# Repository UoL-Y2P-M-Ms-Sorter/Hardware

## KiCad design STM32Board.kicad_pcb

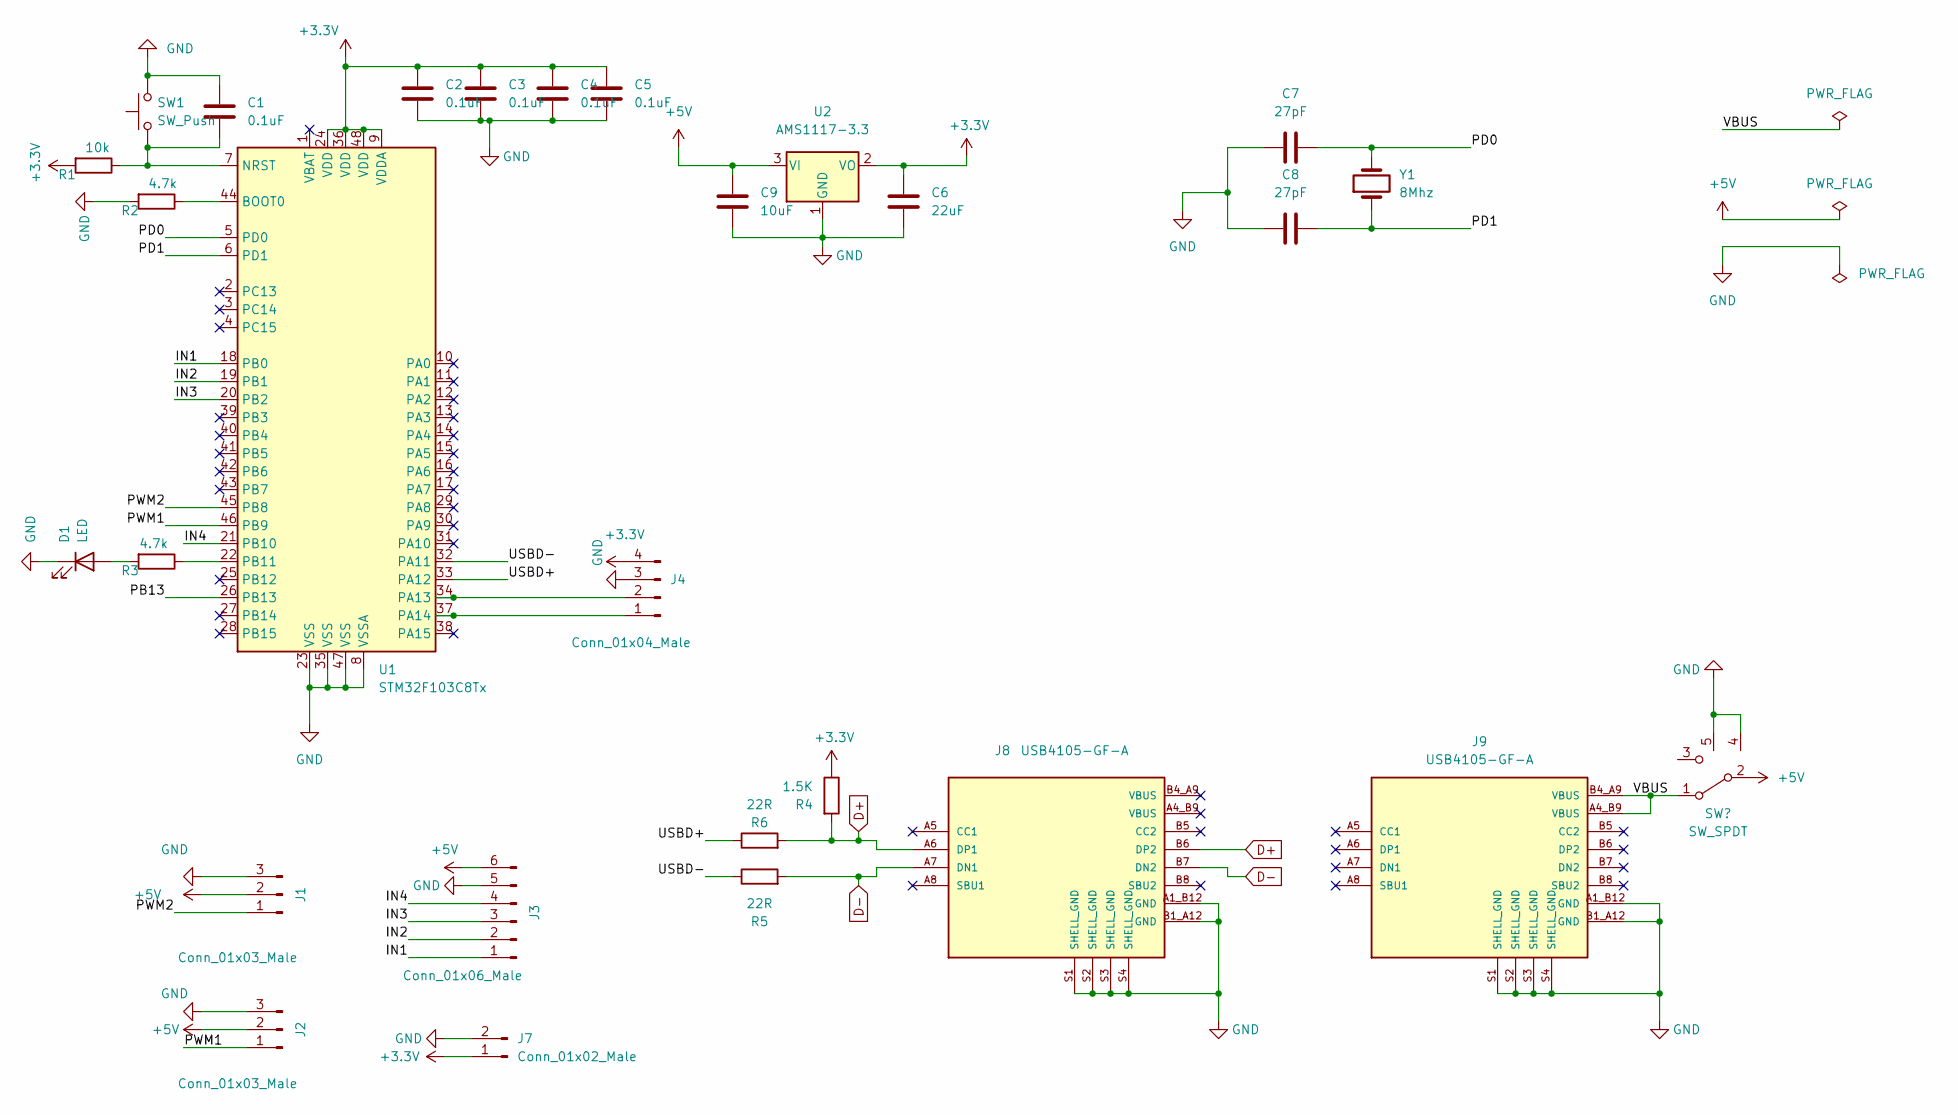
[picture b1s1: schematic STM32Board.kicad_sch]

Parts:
C1, C2, C3, C4, C5: 0.1uF; C_0603_1608Metric
C6: 22uF; CP_EIA-3216-18_Kemet-A
C7, C8: 27pF; C_0603_1608Metric
C9: 10uF; C_0603_1608Metric
D1: LED; LED_0805_2012Metric_Pad1.15x1.40mm_HandSolder
J1, J2: Conn_01x03_Male; PinHeader_1x03_P2.54mm_Vertical
J3: Conn_01x06_Male; PinHeader_1x06_P2.54mm_Vertical
J4: Conn_01x04_Male; PinHeader_1x04_P2.54mm_Vertical
J7: Conn_01x02_Male; PinHeader_1x02_P2.54mm_Vertical
J8, J9: USB4105-GF-A; GCT_USB4105-GF-A; PARTREV A3
R1: 10k; R_0603_1608Metric
R2, R3: 4.7k; R_0603_1608Metric
R4: 1.5K; R_0603_1608Metric
R5, R6: 22R; R_0603_1608Metric
SW1: SW_Push; SW_Push_SPST_NO_Alps_SKRK
U1: STM32F103C8Tx; LQFP-48_7x7mm_P0.5mm
U2: AMS1117-3.3; SOT-223-3_TabPin2
Y1: 8Mhz; Crystal_HC49-4H_Vertical

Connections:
+3V3: C2.2, C3.2, C4.2, C5.2, C6.1, J4.4, J7.1, R1.2, R4.1, U1.9 (VDDA), U1.24 (VDD), U1.36 (VDD), U1.48 (VDD), U2.2 (VO)
+5V: C9.1, J1.2, J2.2, J3.6, U2.3 (VI); also elsewhere on the board
/IN1: J3.1, U1.18 (PB0)
/IN2: J3.2, U1.19 (PB1)
/IN3: J3.3, U1.20 (PB2)
/IN4: J3.4, U1.21 (PB10)
/PB13: U1.26 (PB13)
/PD0: C7.2, U1.5 (PD0), Y1.2
/PD1: C8.2, U1.6 (PD1), Y1.1
/PWM1: J2.1, U1.46 (PB9)
/PWM2: J1.1, U1.45 (PB8)
/USBD+: R6.1, U1.33 (PA12)
/USBD-: R5.1, U1.32 (PA11)
/VBUS: J9.A4_B9 (VBUS), J9.B4_A9 (VBUS); also elsewhere on the board
D+: J8.A6 (DP1), J8.B6 (DP2), R4.2, R6.2
D-: J8.A7 (DN1), J8.B7 (DN2), R5.2
GND: C1.2, C2.1, C3.1, C4.1, C5.1, C6.2, C7.1, C8.1, C9.2, D1.1 (K), J1.3, J2.3, J3.5, J4.3, J7.2, J8.A1_B12 (GND), J8.B1_A12 (GND), J8.S1 (SHELL_GND), J8.S2 (SHELL_GND), J8.S3 (SHELL_GND), J8.S4 (SHELL_GND), J9.A1_B12 (GND), J9.B1_A12 (GND), J9.S1 (SHELL_GND), J9.S2 (SHELL_GND), J9.S3 (SHELL_GND), J9.S4 (SHELL_GND), R2.2, SW1.2, U1.8 (VSSA), U1.23 (VSS), U1.35 (VSS), U1.47 (VSS), U2.1 (GND); also elsewhere on the board
unnamed: C1.1, R1.1, SW1.1, U1.7 (NRST)
unnamed: D1.2 (A), R3.2
unnamed: J4.1, U1.37 (PA14)
unnamed: J4.2, U1.34 (PA13)
unnamed: R2.1, U1.44 (BOOT0)
unnamed: R3.1, U1.22 (PB11)

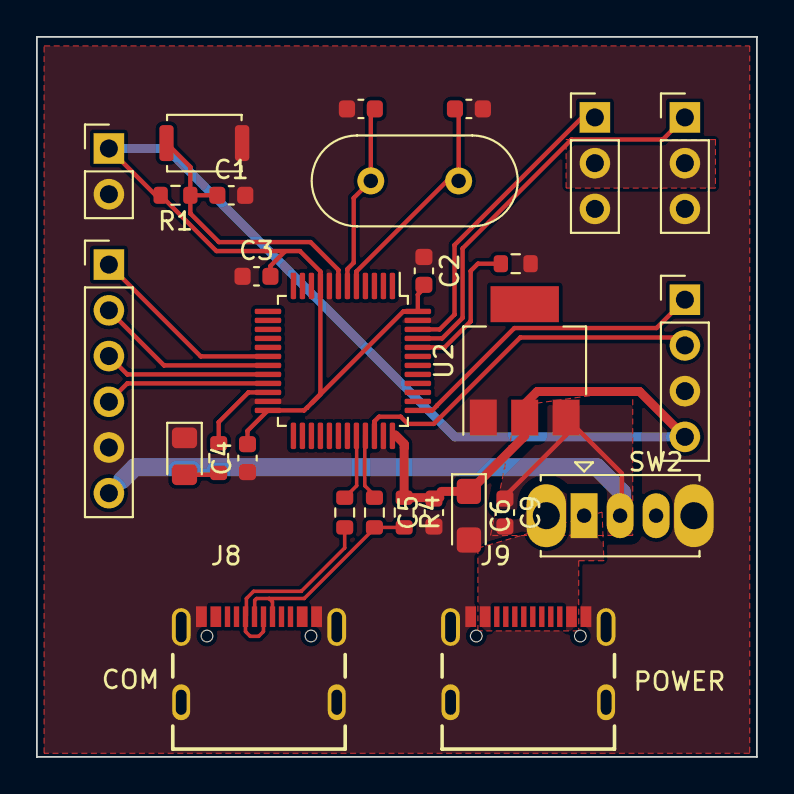
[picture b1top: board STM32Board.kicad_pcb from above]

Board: 2 copper layers, 40.0 x 40.0 mm, 28 parts (0 on the bottom side), 22 nets.

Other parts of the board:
SW2: SW_SPDT; SW_Slide_1P2T_CK_OS102011MS2Q

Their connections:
+5V: SW2.2 (B); also elsewhere on the board
/VBUS: SW2.1 (A); also elsewhere on the board
GND: SW2.4 (SH1), SW2.5 (SH1); also elsewhere on the board

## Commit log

2023-02-03 Complete wirig
2023-02-04 add gitignore file and repair error in schematics
2023-02-04 Add bom file
2023-02-05 Add gerber file, change the 3.3 and gnd def
